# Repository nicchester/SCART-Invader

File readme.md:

# SCART Invader 

An open-hardware RGB SCART multiplexer with features:

- Auto-detection of a video signal on CVBS, CSYNC, YPbPr, or S-Video
- Aspect ratio (pin 8) and RGB/Composite blanking (pin 16) control 
- Support for CVBS -> CSYNC with LM1881 on board (switched in by a relay) 
- IR remote control 
- Fully isolated relay mux design 
- 100% Through-hole design for tedious hand assembly 
- Ultra-compact design 
- Enclosure printable on most home 3D printers 
- 2-layer PCB design for cheap manufacture by your favourite PCB fabricator

---

---

### TODOs

- Implement remote control 
- Implement configuration interface over UART

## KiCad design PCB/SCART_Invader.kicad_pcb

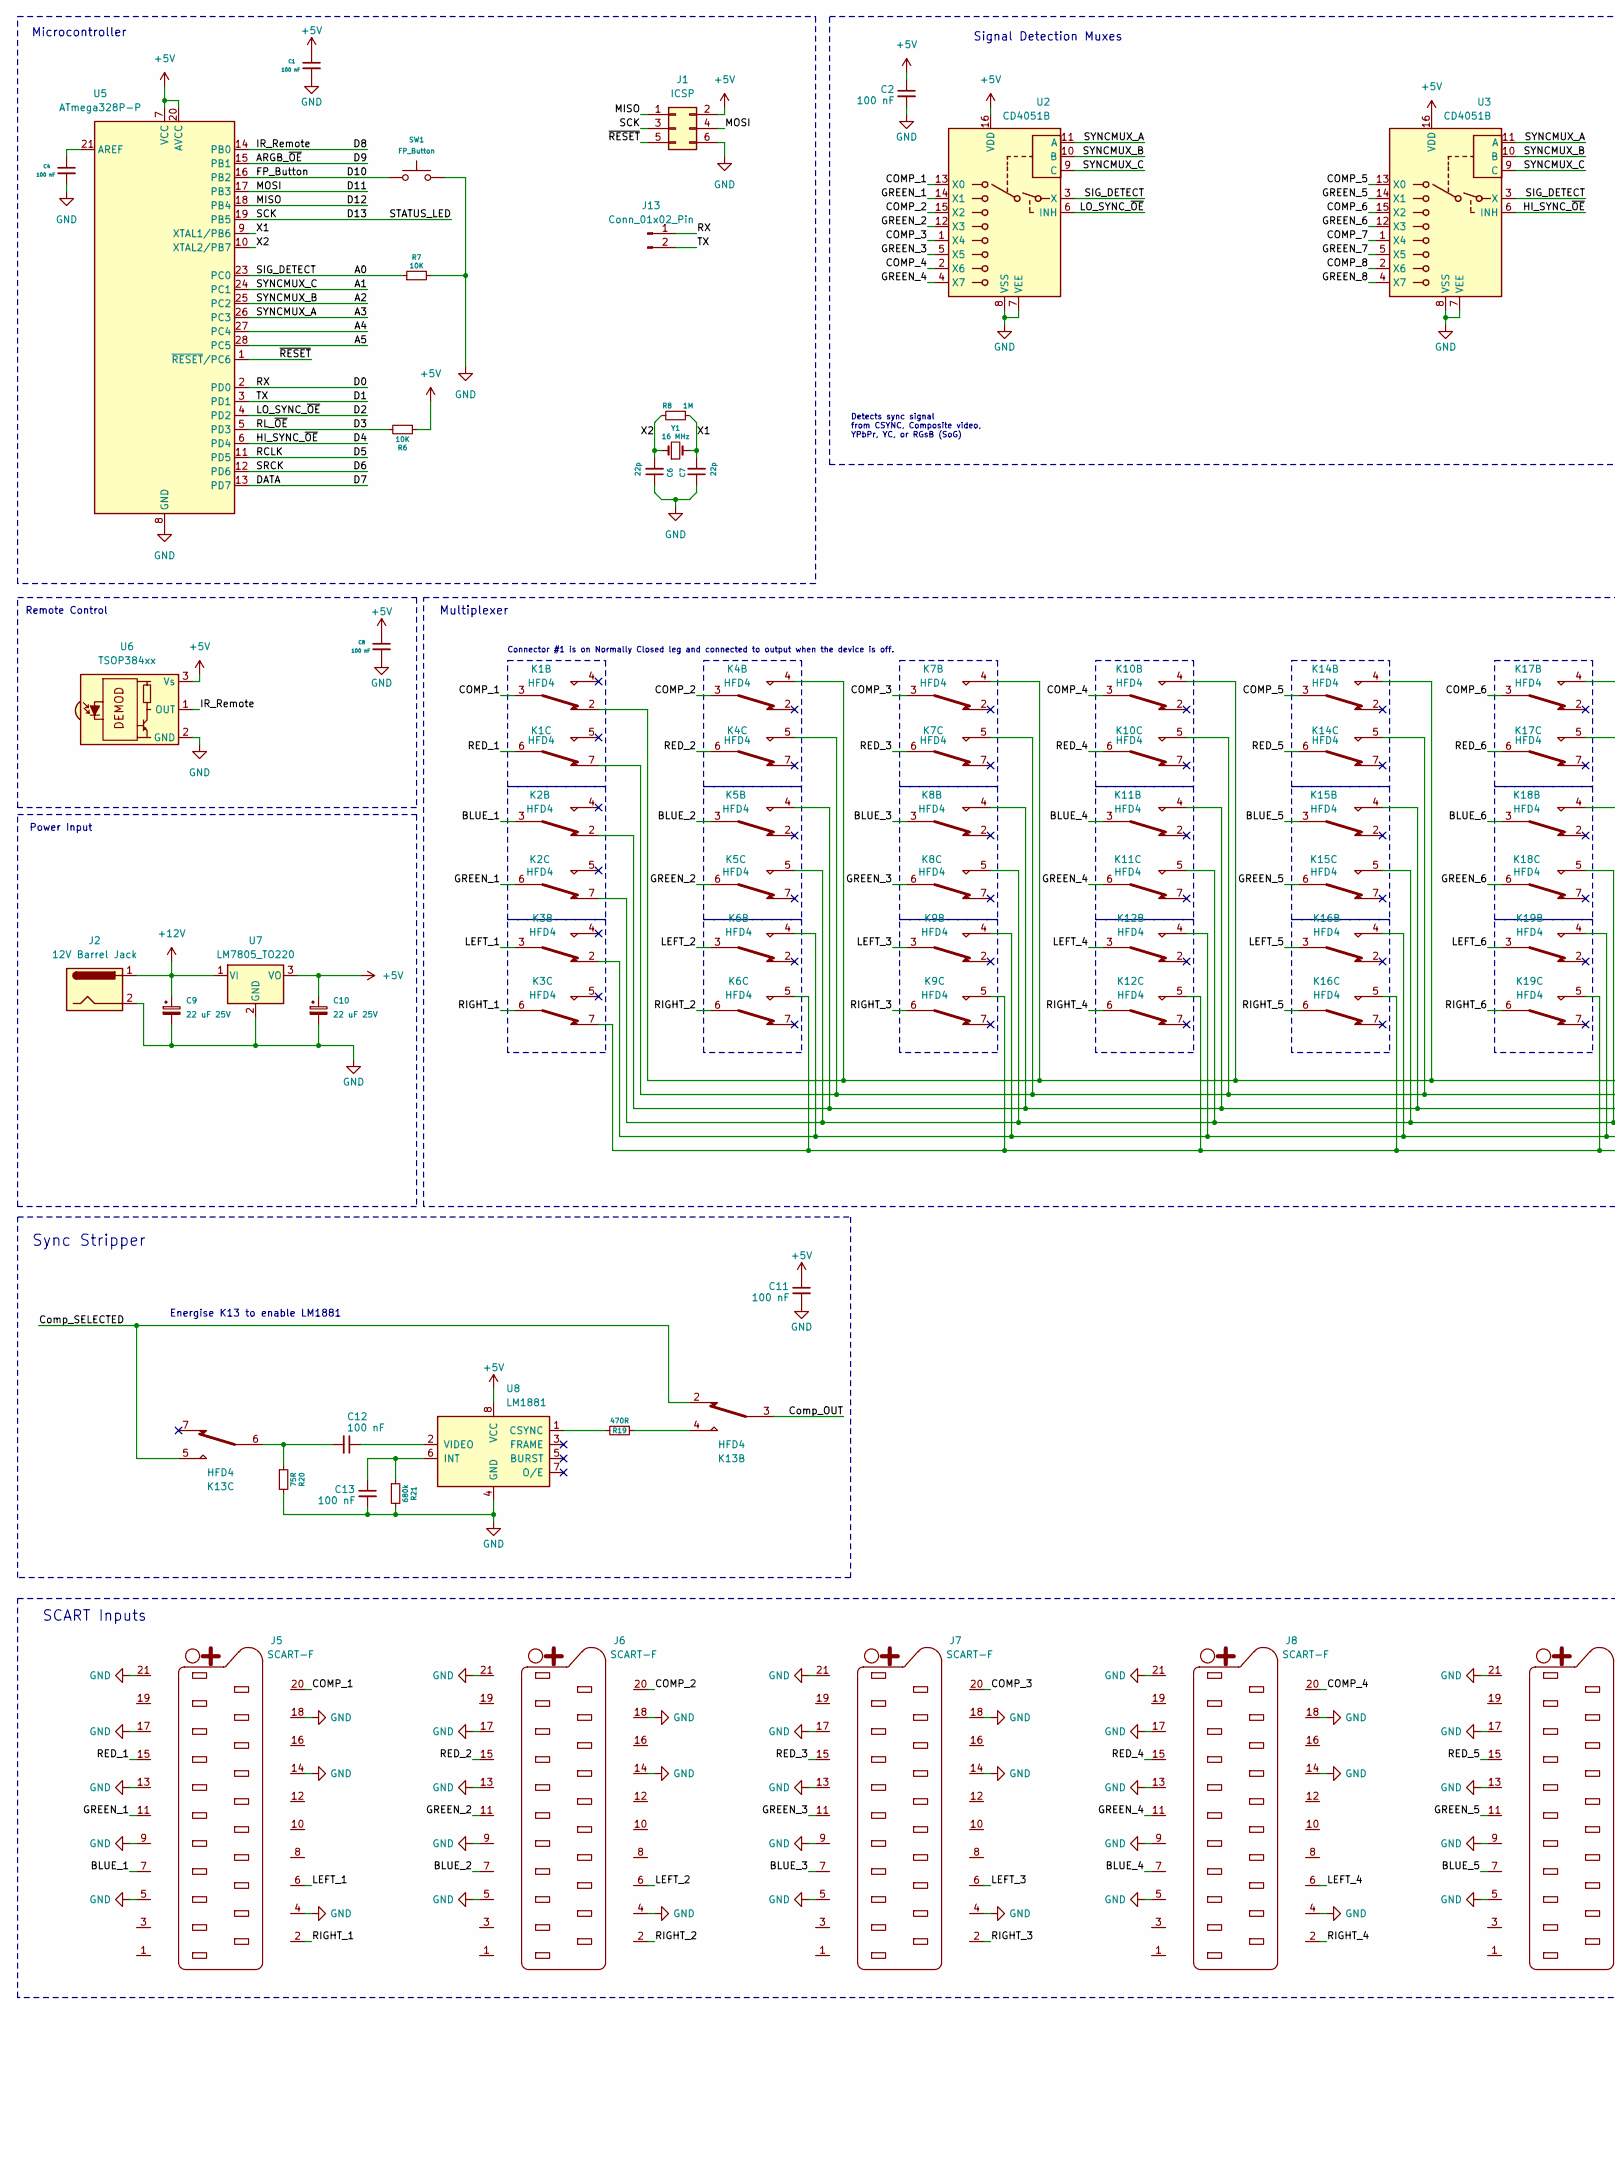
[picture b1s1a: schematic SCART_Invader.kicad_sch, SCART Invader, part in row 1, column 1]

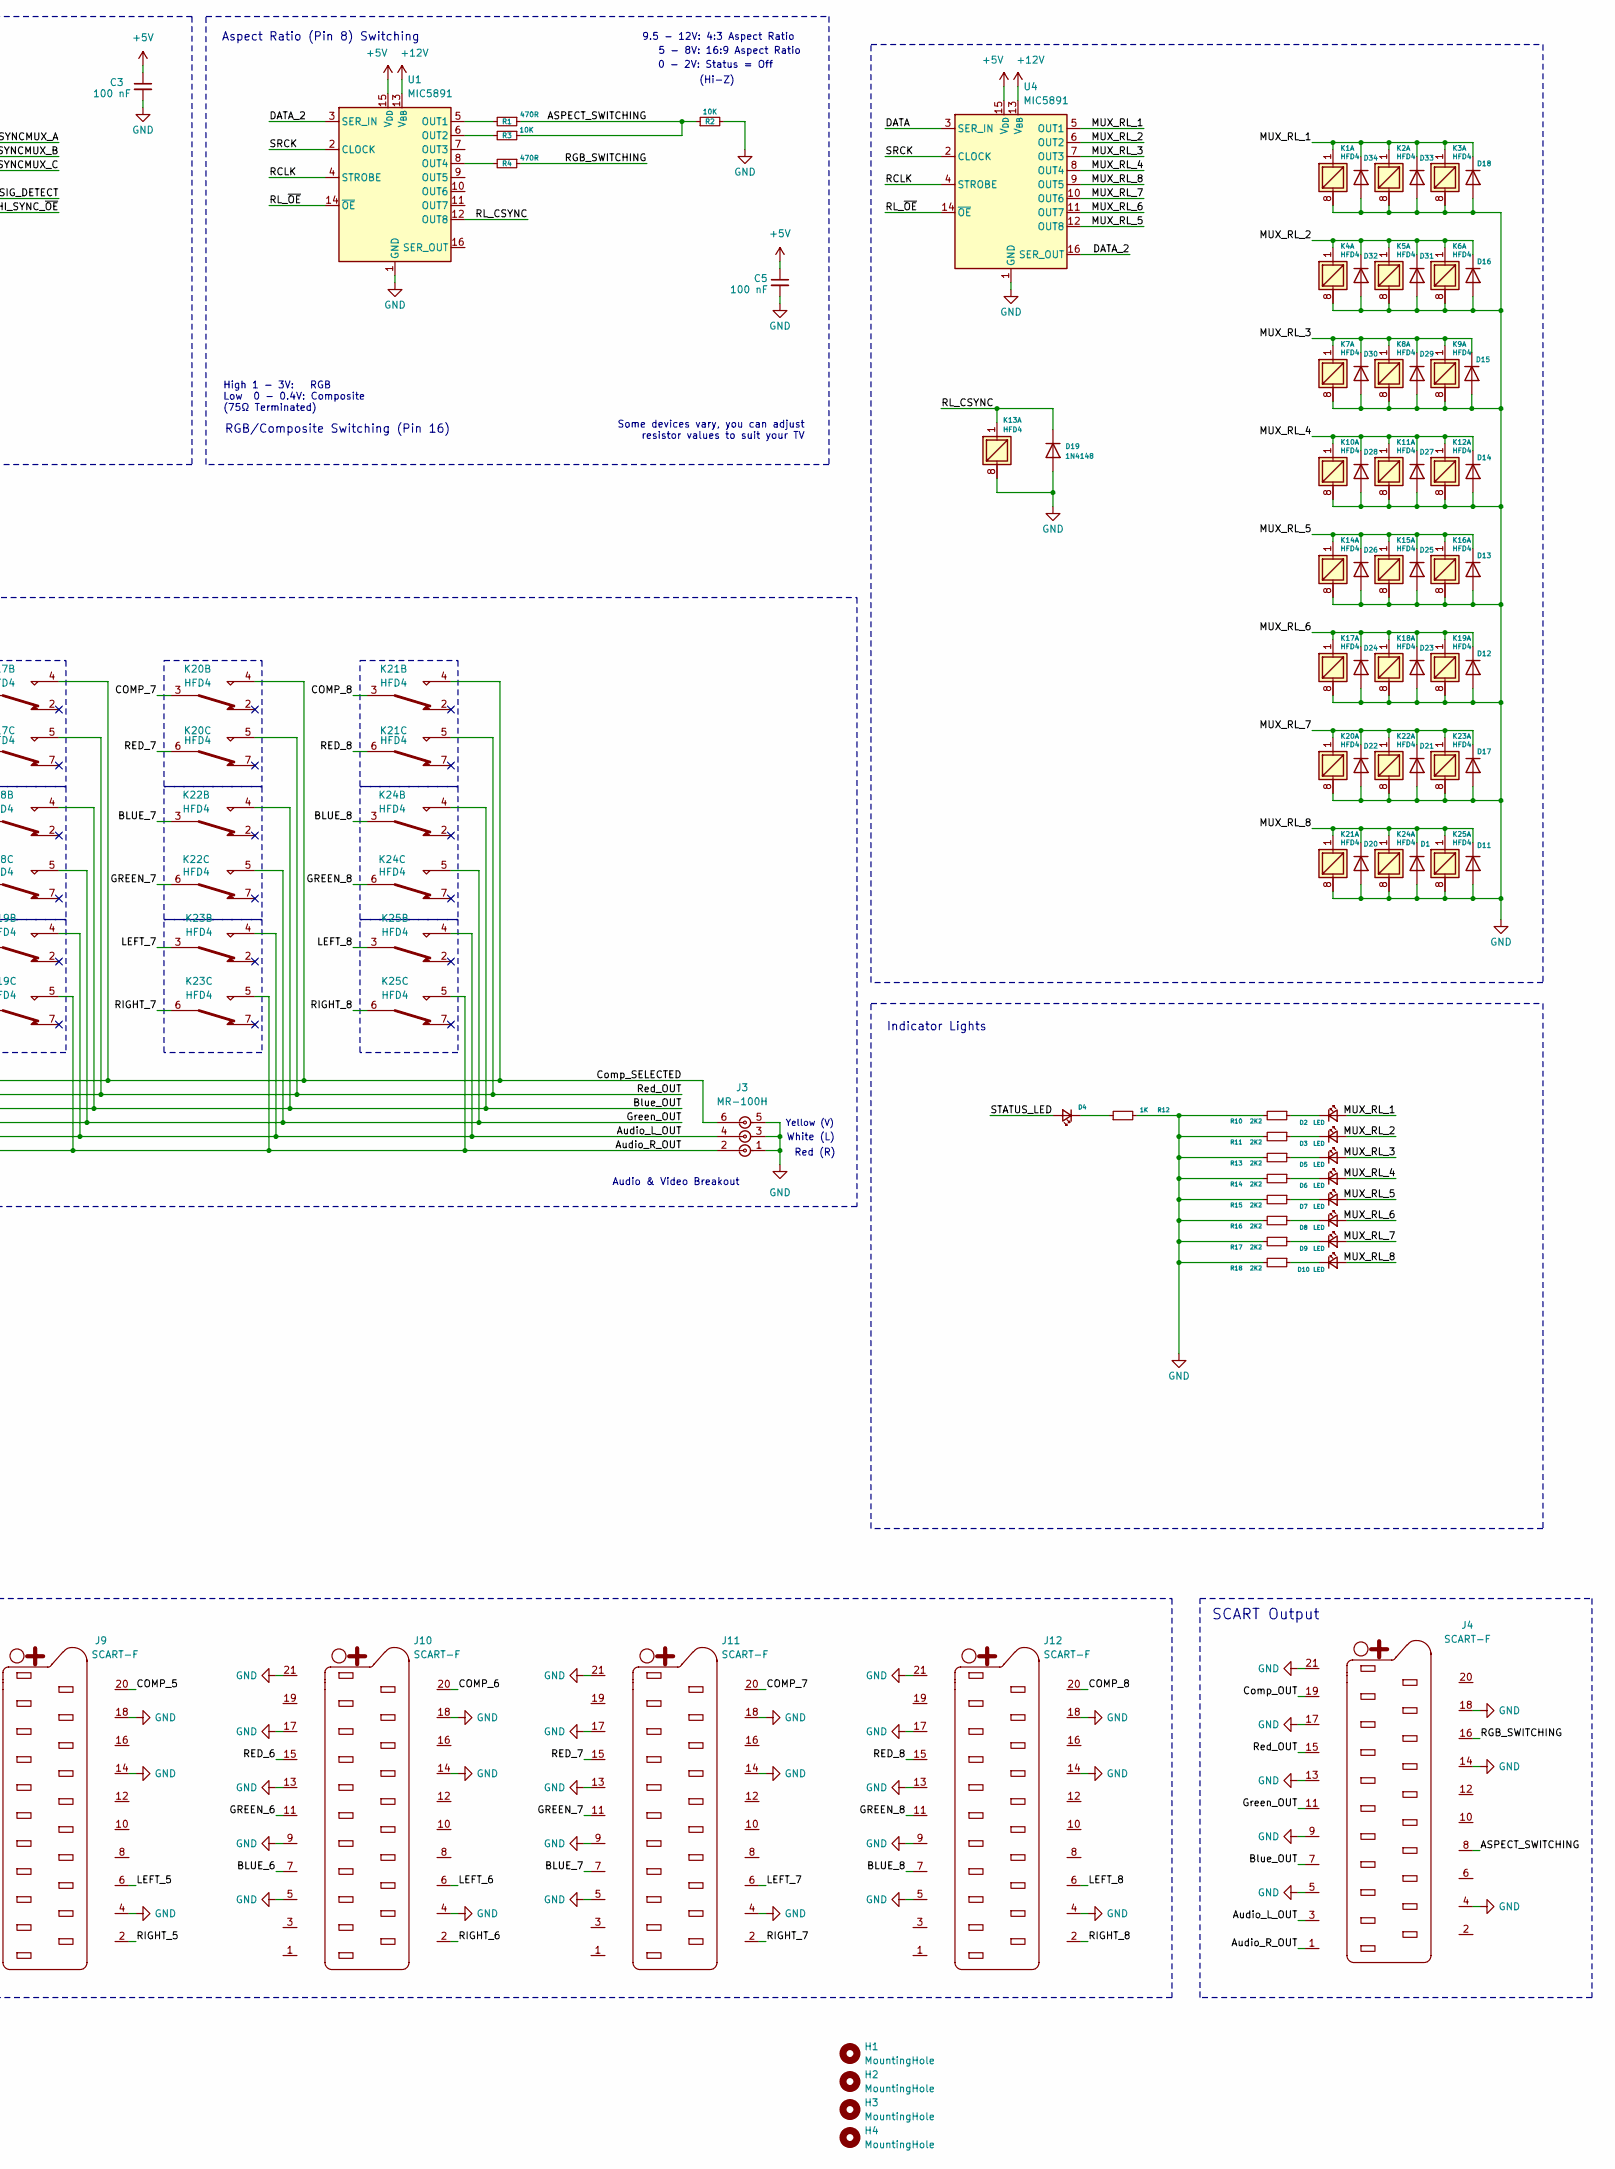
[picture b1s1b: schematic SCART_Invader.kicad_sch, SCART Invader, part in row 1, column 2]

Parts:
C1, C2, C3, C4, C5, C8, C11, C12, C13: 100 nF; C_Disc_D3.0mm_W1.6mm_P2.50mm
C6, C7: 22p; C_Disc_D3.0mm_W1.6mm_P2.50mm
C9, C10: 22 uF 25V; CP_Radial_D5.0mm_P2.50mm
D1, D11, D12, D13, D14, D15, D16, D17, D18, D19, D20, D21, D22, D23, D24, D25, D26, D27, D28, D29, D30, D31, D32, D33, D34: 1N4148; D_DO-35_SOD27_P2.54mm_Vertical_AnodeUp
D2, D3, D5, D6, D7, D8, D9, D10: LED; LED_D3.0mm
D4: Status; LED_D3.0mm
H1, H2, H3, H4: MountingHole; MountingHole_3.2mm_M3
J1: ICSP; PinHeader_2x03_P2.54mm_Vertical
J2: 12V Barrel Jack; BarrelJack_Horizontal
J3: MR-100H; RCJ-32234
J4, J5, J6, J7, J8, J9, J10, J11, J12: SCART-F; SCART_F_Vertical_Wide
J13: Conn_01x02_Pin; PinHeader_1x02_P2.54mm_Vertical
K1, K2, K3, K4, K5, K6, K7, K8, K9, K10, K11, K12, K13, K14, K15, K16, K17, K18, K19, K20, K21, K22, K23, K24, K25: HFD4
R1, R4, R19: 470R; R_Axial_DIN0207_L6.3mm_D2.5mm_P7.62mm_Horizontal
R2, R3, R6, R7: 10K; R_Axial_DIN0207_L6.3mm_D2.5mm_P7.62mm_Horizontal
R8: 1M; R_Axial_DIN0207_L6.3mm_D2.5mm_P7.62mm_Horizontal
R10, R11, R13, R14, R15, R16, R17, R18: 2K2; R_Axial_DIN0207_L6.3mm_D2.5mm_P7.62mm_Horizontal
R12: 1K; R_Axial_DIN0207_L6.3mm_D2.5mm_P7.62mm_Horizontal
R20: 75R; R_Axial_DIN0207_L6.3mm_D2.5mm_P7.62mm_Horizontal
R21: 680k; R_Axial_DIN0207_L6.3mm_D2.5mm_P7.62mm_Horizontal
SW1: FP_Button; SW_Tactile_SKHH_Angled
U1, U4: MIC5891; DIP-16_W7.62mm
U2, U3: CD4051B; DIP-16_W7.62mm
U5: ATmega328P-P; DIP-28_W7.62mm
U6: TSOP384xx; Vishay_MINICAST-3Pin
U7: LM7805_TO220; TO-220-3_Horizontal_TabDown
U8: LM1881; DIP-8_W7.62mm
Y1: 16 MHz; Crystal_HC49-U_Vertical

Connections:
+5V: C1.1, C2.1, C3.1, C5.1, C8.1, C10.1, C11.1, J1.2, R6.1, U1.15 (V_{DD}), U2.16 (VDD), U3.16 (VDD), U4.15 (V_{DD}), U5.7 (VCC), U5.20 (AVCC), U6.3 (Vs), U7.3 (VO), U8.8 (VCC)
+12V: C9.1, J2.1, U1.13 (V_{BB}), U4.13 (V_{BB}), U7.1 (VI)
/A0: R7.1, U2.3 (X), U3.3 (X), U5.23 (PC0)
/A1: U2.9 (C), U3.9 (C), U5.24 (PC1)
/A2: U2.10 (B), U3.10 (B), U5.25 (PC2)
/A3: U2.11 (A), U3.11 (A), U5.26 (PC3)
/A4: U5.27 (PC4)
/A5: U5.28 (PC5)
/ARGB_~OE: U5.15 (PB1)
/ASPECT_SWITCHING: J4.8, R1.1, R2.1, R3.1
/Audio_L_OUT: J3.4, J4.3, K3.2, K6.4, K9.4, K12.4, K16.4, K19.4, K23.4, K25.4
/Audio_R_OUT: J3.2, J4.1, K3.7, K6.5, K9.5, K12.5, K16.5, K19.5, K23.5, K25.5
/BLUE_1: J5.7, K2.3
/BLUE_2: J6.7, K5.3
/BLUE_3: J7.7, K8.3
/BLUE_4: J8.7, K11.3
/BLUE_5: J9.7, K15.3
/BLUE_6: J10.7, K18.3
/BLUE_7: J11.7, K22.3
/BLUE_8: J12.7, K24.3
/Blue_OUT: J4.7, K2.2, K5.4, K8.4, K11.4, K15.4, K18.4, K22.4, K24.4
/COMP_1: J5.20, K1.3, U2.13 (X0)
/COMP_2: J6.20, K4.3, U2.15 (X2)
/COMP_3: J7.20, K7.3, U2.1 (X4)
/COMP_4: J8.20, K10.3, U2.2 (X6)
/COMP_5: J9.20, K14.3, U3.13 (X0)
/COMP_6: J10.20, K17.3, U3.15 (X2)
/COMP_7: J11.20, K20.3, U3.1 (X4)
/COMP_8: J12.20, K21.3, U3.2 (X6)
/Comp_OUT: J4.19, K13.3
/Comp_SELECTED: J3.6, K1.2, K4.4, K7.4, K10.4, K13.2, K13.5, K14.4, K17.4, K20.4, K21.4
/D0: J13.1, U5.2 (PD0)
/D1: J13.2, U5.3 (PD1)
/D2: U2.6 (INH), U5.4 (PD2)
/D3: R6.2, U1.14 (~OE), U4.14 (~OE), U5.5 (PD3)
/D4: U3.6 (INH), U5.6 (PD4)
/D5: U1.4 (STROBE), U4.4 (STROBE), U5.11 (PD5)
/D6: U1.2 (CLOCK), U4.2 (CLOCK), U5.12 (PD6)
/D7: U4.3 (SER_IN), U5.13 (PD7)
/D8: U5.14 (PB0), U6.1 (OUT)
/D10: SW1.1, U5.16 (PB2)
/D11: J1.4, U5.17 (PB3)
/D12: J1.1, U5.18 (PB4)
/D13: D4.2 (A), J1.3, U5.19 (PB5)
/DATA_2: U1.3 (SER_IN), U4.16 (SER_OUT)
/GREEN_1: J5.11, K2.6, U2.14 (X1)
/GREEN_2: J6.11, K5.6, U2.12 (X3)
/GREEN_3: J7.11, K8.6, U2.5 (X5)
/GREEN_4: J8.11, K11.6, U2.4 (X7)
/GREEN_5: J9.11, K15.6, U3.14 (X1)
/GREEN_6: J10.11, K18.6, U3.12 (X3)
/GREEN_7: J11.11, K22.6, U3.5 (X5)
/GREEN_8: J12.11, K24.6, U3.4 (X7)
/Green_OUT: J4.11, K2.7, K5.5, K8.5, K11.5, K15.5, K18.5, K22.5, K24.5
/LEFT_1: J5.6, K3.3
/LEFT_2: J6.6, K6.3
/LEFT_3: J7.6, K9.3
/LEFT_4: J8.6, K12.3
/LEFT_5: J9.6, K16.3
/LEFT_6: J10.6, K19.3
/LEFT_7: J11.6, K23.3
/LEFT_8: J12.6, K25.3
/MUX_RL_1: D2.2 (A), D18.1 (K), D33.1 (K), D34.1 (K), K1.1, K2.1, K3.1, U4.5 (OUT1)
/MUX_RL_2: D3.2 (A), D16.1 (K), D31.1 (K), D32.1 (K), K4.1, K5.1, K6.1, U4.6 (OUT2)
/MUX_RL_3: D5.2 (A), D15.1 (K), D29.1 (K), D30.1 (K), K7.1, K8.1, K9.1, U4.7 (OUT3)
/MUX_RL_4: D6.2 (A), D14.1 (K), D27.1 (K), D28.1 (K), K10.1, K11.1, K12.1, U4.8 (OUT4)
/MUX_RL_5: D7.2 (A), D13.1 (K), D25.1 (K), D26.1 (K), K14.1, K15.1, K16.1, U4.12 (OUT8)
/MUX_RL_6: D8.2 (A), D12.1 (K), D23.1 (K), D24.1 (K), K17.1, K18.1, K19.1, U4.11 (OUT7)
/MUX_RL_7: D9.2 (A), D17.1 (K), D21.1 (K), D22.1 (K), K20.1, K22.1, K23.1, U4.10 (OUT6)
/MUX_RL_8: D1.1 (K), D10.2 (A), D11.1 (K), D20.1 (K), K21.1, K24.1, K25.1, U4.9 (OUT5)
/RED_1: J5.15, K1.6
/RED_2: J6.15, K4.6
/RED_3: J7.15, K7.6
/RED_4: J8.15, K10.6
/RED_5: J9.15, K14.6
/RED_6: J10.15, K17.6
/RED_7: J11.15, K20.6
/RED_8: J12.15, K21.6
/RGB_SWITCHING: J4.16, R4.1
/RIGHT_1: J5.2, K3.6
/RIGHT_2: J6.2, K6.6
/RIGHT_3: J7.2, K9.6
/RIGHT_4: J8.2, K12.6
/RIGHT_5: J9.2, K16.6
/RIGHT_6: J10.2, K19.6
/RIGHT_7: J11.2, K23.6
/RIGHT_8: J12.2, K25.6
/RL_CSYNC: D19.1 (K), K13.1, U1.12 (OUT8)
/Red_OUT: J4.15, K1.7, K4.5, K7.5, K10.5, K14.5, K17.5, K20.5, K21.5
/X1: C7.2, R8.1, U5.9 (XTAL1/PB6), Y1.2
/X2: C6.2, R8.2, U5.10 (XTAL2/PB7), Y1.1
/~RESET: J1.5, U5.1 (~RESET/PC6)
GND: C1.2, C2.2, C3.2, C4.2, C5.2, C6.1, C7.1, C8.2, C9.2, C10.2, C11.2, C13.2, D1.2 (A), D11.2 (A), D12.2 (A), D13.2 (A), D14.2 (A), D15.2 (A), D16.2 (A), D17.2 (A), D18.2 (A), D19.2 (A), D20.2 (A), D21.2 (A), D22.2 (A), D23.2 (A), D24.2 (A), D25.2 (A), D26.2 (A), D27.2 (A), D28.2 (A), D29.2 (A), D30.2 (A), D31.2 (A), D32.2 (A), D33.2 (A), D34.2 (A), J1.6, J2.2, J3.1, J3.3, J3.5, J4.4, J4.5, J4.9, J4.13, J4.14, J4.17, J4.18, J4.21, J5.4, J5.5, J5.9, J5.13, J5.14, J5.17, J5.18, J5.21, J6.4, J6.5, J6.9, J6.13, J6.14, J6.17, J6.18, J6.21, J7.4, J7.5, J7.9, J7.13, J7.14, J7.17, J7.18, J7.21, J8.4, J8.5, J8.9, J8.13, J8.14, J8.17, J8.18, J8.21, J9.4, J9.5, J9.9, J9.13, J9.14, J9.17, J9.18, J9.21, J10.4, J10.5, J10.9, J10.13, J10.14, J10.17, J10.18, J10.21, J11.4, J11.5, J11.9, J11.13, J11.14, J11.17, J11.18, J11.21, J12.4, J12.5, J12.9, J12.13, J12.14, J12.17, J12.18, J12.21, K1.8, K2.8, K3.8, K4.8, K5.8, K6.8, K7.8, K8.8, K9.8, K10.8, K11.8, K12.8, K13.8, K14.8, K15.8, K16.8, K17.8, K18.8, K19.8, K20.8, K21.8, K22.8, K23.8, K24.8, K25.8, R2.2, R7.2, R10.2, R11.2, R12.2, R13.2, R14.2, R15.2, R16.2, R17.2, R18.2, R20.2, R21.2, SW1.2, U1.1 (GND), U2.7 (VEE), U2.8 (VSS), U3.7 (VEE), U3.8 (VSS), U4.1 (GND), U5.8 (GND), U5.22 (GND), U6.2 (GND), U7.2 (GND), U8.4 (GND)
unnamed: C12.2, K13.6, R20.1
unnamed: D2.1 (K), R10.1
unnamed: D3.1 (K), R11.1
unnamed: D4.1 (K), R12.1
unnamed: D5.1 (K), R13.1
unnamed: D6.1 (K), R14.1
unnamed: D7.1 (K), R15.1
unnamed: D8.1 (K), R16.1
unnamed: D9.1 (K), R17.1
unnamed: D10.1 (K), R18.1
unnamed: K13.4, R19.1
unnamed: R1.2, U1.5 (OUT1)
unnamed: R3.2, U1.6 (OUT2)
unnamed: R4.2, U1.8 (OUT4)
unnamed: C4.1, U5.21 (AREF)
unnamed: R19.2, U8.1 (CSYNC)
unnamed: C13.1, R21.1, U8.6 (INT)
unnamed: C12.1, U8.2 (VIDEO)

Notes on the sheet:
Microcontroller
0 - 2V: Status = Off
Sync Stripper
Remote Control
9.5 - 12V: 4:3 Aspect Ratio
SCART Output
(Hi-Z)
Detects sync signal from CSYNC, Composite video, YPbPr, YC, or RGsB (SoG)
Energise K13 to enable LM1881
Audio & Video Breakout
Yellow (V)
5 - 8V: 16:9 Aspect Ratio
Power Input
High 1 - 3V: RGB Low 0 - 0.4V: Composite (75Ω Terminated)
Some devices vary, you can adjust resistor values to suit your TV
Multiplexer
Red (R)
Connector #1 is on Normally Closed leg and connected to output when the device is off.
RGB/Composite Switching (Pin 16)
SCART Inputs
Indicator Lights
White (L)
Aspect Ratio (Pin 8) Switching
Signal Detection Muxes

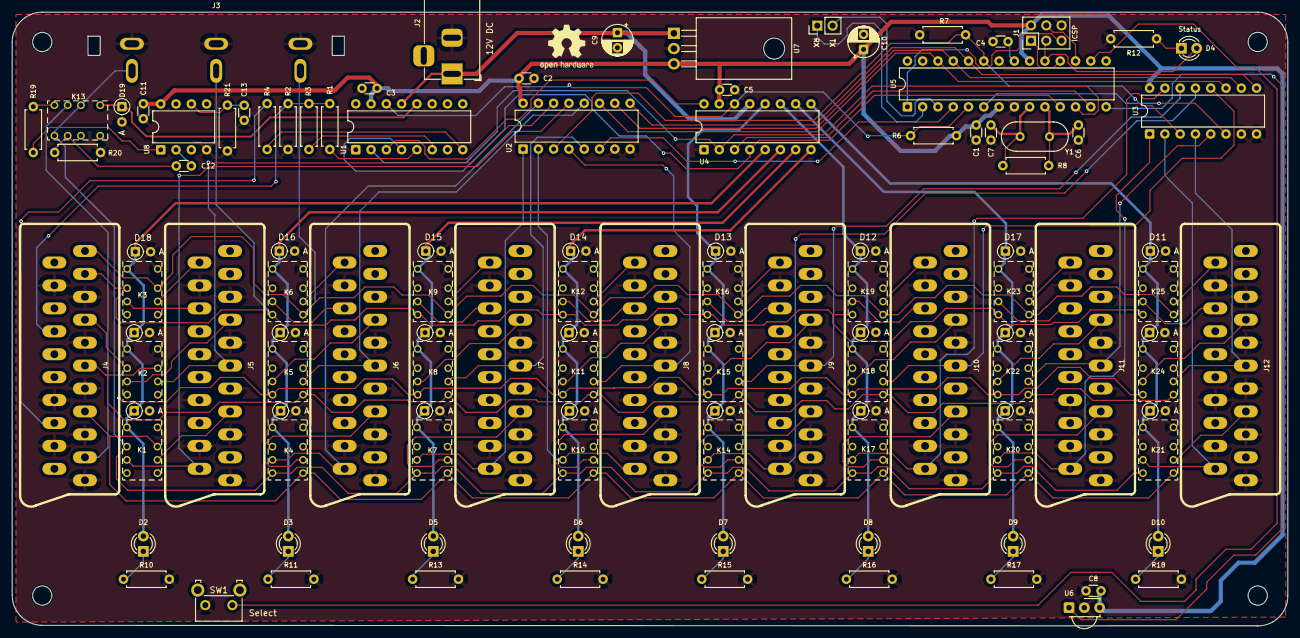
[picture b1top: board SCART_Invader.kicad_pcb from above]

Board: 2 copper layers, 212.0 x 102.0 mm, 118 parts (0 on the bottom side), 108 nets.

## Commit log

2025-11-09 Adds project files and readme
2025-11-09 Fixes bug where the device will lock onto a detected signal too quickly while switching through 'auto' mode
2025-11-13 Updates readme, adds top cover
2026-01-04 Updates top cover
2026-01-04 Adds images to readme
2026-01-04 Some refactoring, adds EEPROM and IR remote functionality
2026-01-04 Fixes remote not working, adds blink on status LED to confirm mode switches
